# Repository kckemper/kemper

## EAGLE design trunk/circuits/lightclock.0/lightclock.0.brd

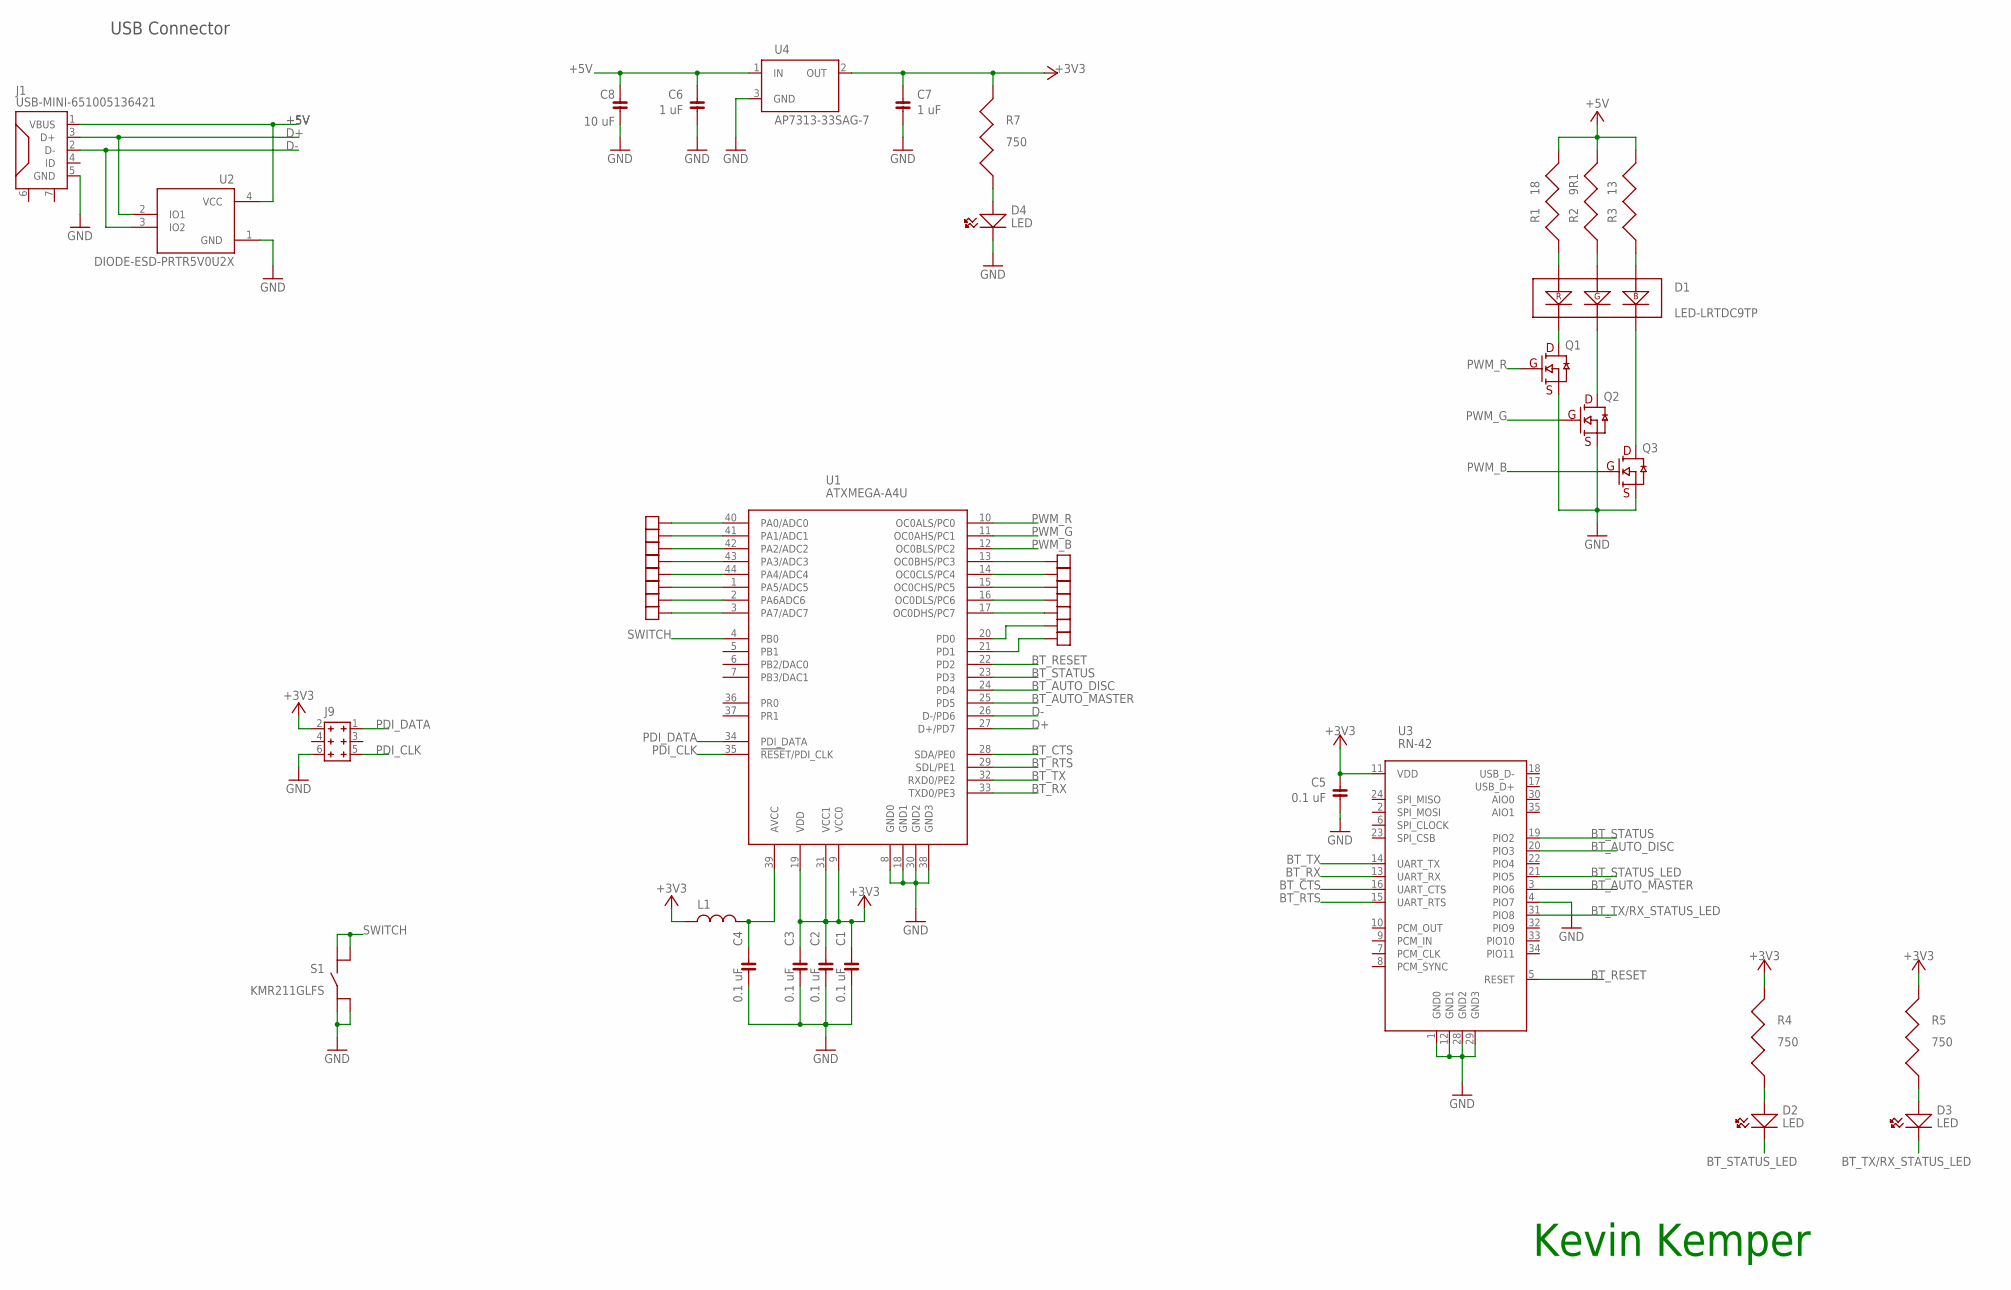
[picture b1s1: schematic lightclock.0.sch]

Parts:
C1, C2, C3, C4, C5: 0.1 uF; 0603
C6, C7: 1 uF; 0603
C8: 10 uF; 0805
D1: LED-LRTDC9TP; LRTDC9TP-EAFB-GHQN
D2, D3, D4: LED; 0603-POL
J1: USB-MINI-651005136421; 651005136421
J2, J3, J4, J5, J6, J7, J8, J10, J11, J12, J13, J14, J15, J16, J17: TESTPAD; HEADER-1X1
J9: HEADER-2X6
L1: IND-0603; 0603
Q1, Q2, Q3: BSS138; SOT-23
R1: 18; 2010
R2: 9R1; 2010
R3: 13; 2010
R4, R5, R7: 750; 0603
S1: KMR211GLFS
U1: ATXMEGA-A4U; ATXMEGA16A4U-AUR
U2: DIODE-ESD-PRTR5V0U2X; PRTR5V0U2X
U3: RN-42
U4: AP7313-33SAG-7

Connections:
+3V3: C1.1, C2.1, C3.1, C5.1, C7.1, J9.2, L1.1, R4.2, R5.2, R7.2, U1.9 (VCC0), U1.19 (VDD), U1.31 (VCC1), U3.11 (VDD), U4.2 (OUT); also elsewhere on the board
+5V: C6.1, C8.1, J1.1 (VBUS), R1.2, R2.2, R3.2, U2.4 (VCC), U4.1 (IN)
BT_AUTO_DISC: U1.24 (PD4), U3.20 (PIO3)
BT_AUTO_MASTER: U1.25 (PD5), U3.3 (PIO6)
BT_CTS: U1.28 (SDA/PE0), U3.16 (UART_CTS)
BT_RESET: U1.22 (PD2), U3.5 (RESET)
BT_RTS: U1.29 (SDL/PE1), U3.15 (UART_RTS)
BT_RX: U1.33 (TXD0/PE3), U3.13 (UART_RX)
BT_STATUS: U1.23 (PD3), U3.19 (PIO2)
BT_STATUS_LED: D2.2, U3.21 (PIO5)
BT_TX: U1.32 (RXD0/PE2), U3.14 (UART_TX)
BT_TX/RX_STATUS_LED: D3.2, U3.31 (PIO8)
D+: J1.3 (D+), U1.27 (D+/PD7), U2.2 (IO1)
D-: J1.2 (D-), U1.26 (D-/PD6), U2.3 (IO2)
GND: C1.2, C2.2, C3.2, C4.2, C5.2, C6.2, C7.2, C8.2, D4.2, J1.5 (GND), J9.6, Q1.2 (S), Q2.2 (S), Q3.2 (S), S1.1, S1.2, U1.8 (GND0), U1.18 (GND1), U1.30 (GND2), U1.38 (GND3), U2.1 (GND), U3.1 (GND0), U3.4 (PIO7), U3.12 (GND1), U3.28 (GND2), U3.29 (GND3), U4.3 (GND); also elsewhere on the board
unnamed: C4.1, L1.2, U1.39 (AVCC)
unnamed: D2.1, R4.1
unnamed: D1.A1, R1.1
unnamed: D1.A2, R2.1
unnamed: D1.A3, R3.1
unnamed: D3.1, R5.1
unnamed: D1.C1, Q1.3 (D)
unnamed: D1.C2, Q2.3 (D)
unnamed: D1.C3, Q3.3 (D)
unnamed: D4.1, R7.1
unnamed: J7.1, U1.20 (PD0)
unnamed: J8.1, U1.21 (PD1)
unnamed: J6.1, U1.17 (OC0DHS/PC7)
unnamed: J5.1, U1.16 (OC0DLS/PC6)
unnamed: J4.1, U1.15 (OC0CHS/PC5)
unnamed: J3.1, U1.14 (OC0CLS/PC4)
unnamed: J2.1, U1.13 (OC0BHS/PC3)
unnamed: J10.1, U1.40 (PA0/ADC0)
unnamed: J11.1, U1.41 (PA1/ADC1)
unnamed: J12.1, U1.42 (PA2/ADC2)
unnamed: J13.1, U1.43 (PA3/ADC3)
unnamed: J14.1, U1.44 (PA4/ADC4)
unnamed: J15.1, U1.1 (PA5/ADC5)
unnamed: J16.1, U1.2 (PA6ADC6)
unnamed: J17.1, U1.3 (PA7/ADC7)
PDI_CLK: J9.5, U1.35 (!RESE!T/PDI_CLK)
PDI_DATA: J9.1, U1.34 (PDI_DATA)
PWM_B: Q3.1 (G), U1.12 (OC0BLS/PC2)
PWM_G: Q2.1 (G), U1.11 (OC0AHS/PC1)
PWM_R: Q1.1 (G), U1.10 (OC0ALS/PC0)
SWITCH: S1.3, S1.4, U1.4 (PB0)

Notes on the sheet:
Kevin Kemper
USB Connector

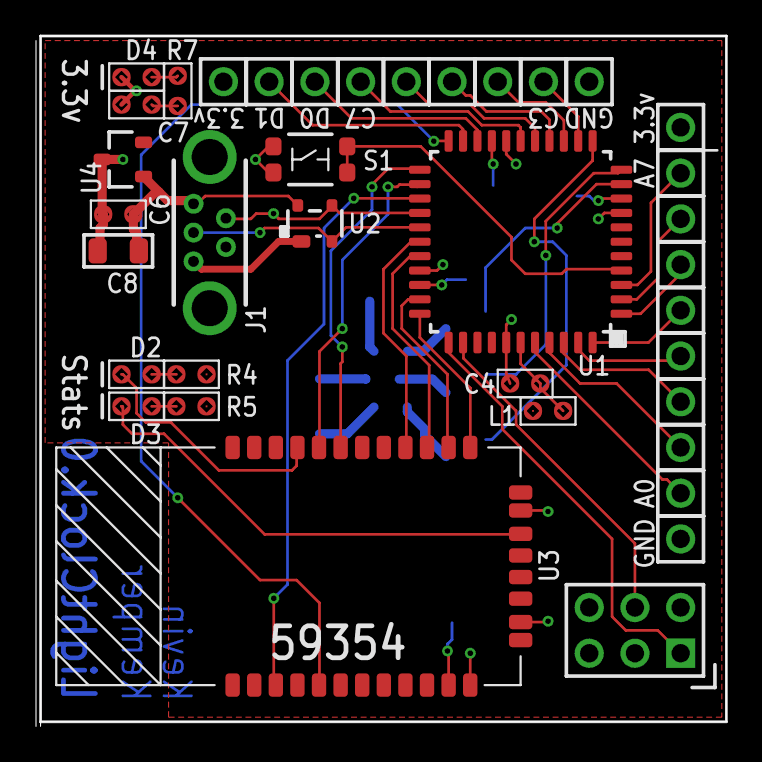
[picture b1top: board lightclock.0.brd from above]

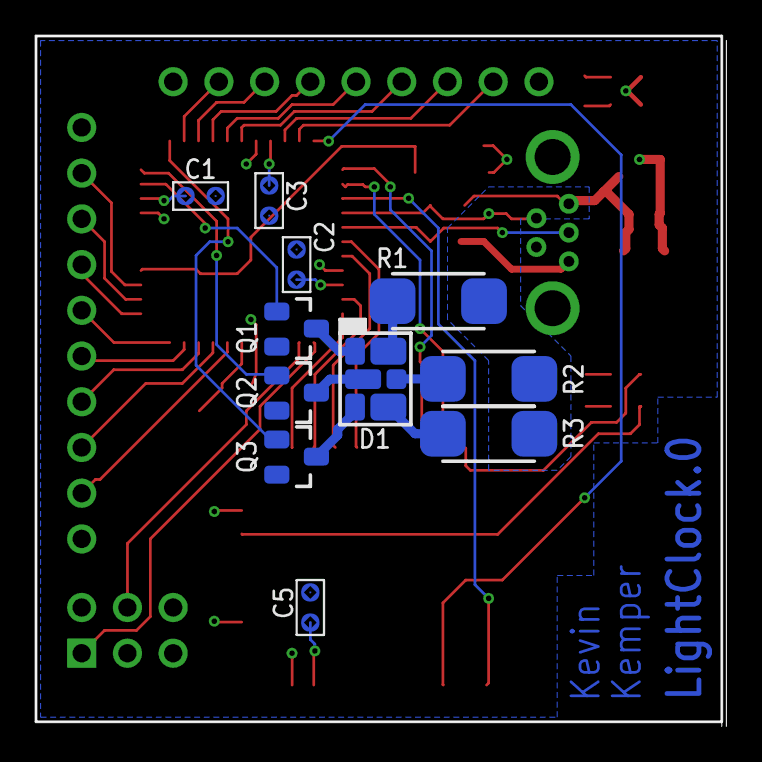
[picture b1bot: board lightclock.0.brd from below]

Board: 2 copper layers, 38.4 x 38.4 mm, 48 parts (11 on the bottom side), 46 nets.

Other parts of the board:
J18, J19, J20, J21: TESTPAD; HEADER-1X1

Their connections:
+3V3: J18.1, J20.1; also elsewhere on the board
GND: J19.1, J21.1; also elsewhere on the board

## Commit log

2011-07-24 Initial directory structure.
2011-07-24 gathering old work from beaversource
2011-07-27 added a gantt
2011-08-31 added some medulla firmware
2011-08-31 adding the base files for the grizzle test
2011-09-05 removed gantchart
2012-08-19 added a lib for eagle
2012-08-19 added the base project for the lightclock
2012-08-24 Created wiki page through web user interface.
2012-09-14 added lightclock board file
2012-09-14 almost done with layout, just needs a review
2012-09-21 final lightclock.0
2012-10-01 Edited wiki page LightClock through web user interface.
2016-02-22 Migrating wiki contents from Google Code
